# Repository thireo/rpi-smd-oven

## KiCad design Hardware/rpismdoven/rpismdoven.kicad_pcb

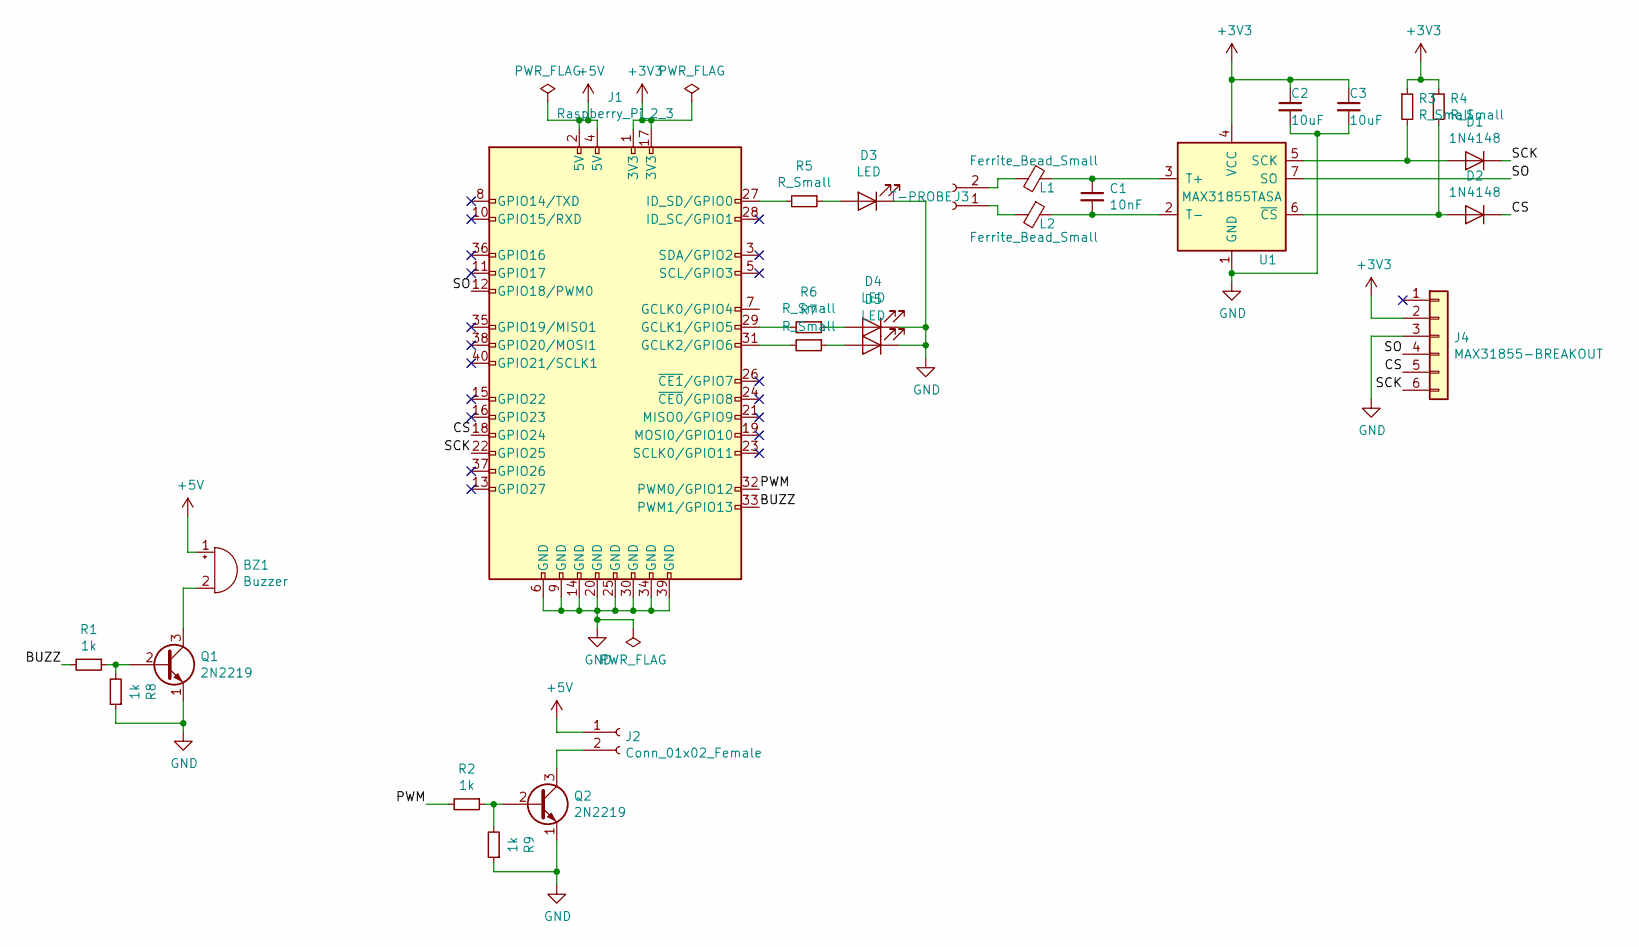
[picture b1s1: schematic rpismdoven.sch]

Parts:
BZ1: Buzzer; Buzzer_12x9.5RM7.6
C1: 10nF; C_0603_1608Metric
C2, C3: 10uF; C_0603_1608Metric
D1, D2: 1N4148; D_DO-35_SOD27_P7.62mm_Horizontal
D3, D4, D5: LED; D_1206_3216Metric
J1: Raspberry_Pi_2_3; PinSocket_2x20_P2.54mm_Vertical
J2: Conn_01x02_Female; TerminalBlock_bornier-2_P5.08mm
J3: T-PROBE; TerminalBlock_bornier-2_P5.08mm
J4: MAX31855-BREAKOUT; PinSocket_1x06_P2.54mm_Vertical
L1, L2: Ferrite_Bead_Small; L_0603_1608Metric
Q1, Q2: 2N2219; TO-92
R1, R2, R8, R9: 1k; R_0603_1608Metric
R3, R4, R5, R6, R7: R_Small; R_0603_1608Metric
U1: MAX31855TASA; SOIC-8_3.9x4.9mm_P1.27mm

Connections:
+3V3: C2.1, C3.1, J1.1 (3V3), J1.17 (3V3), J4.2, R3.1, R4.1, U1.4 (VCC)
+5V: BZ1.1 (-), J1.2 (5V), J1.4 (5V), J2.1
/BUZZ: J1.33 (PWM1/GPIO13), R1.2
/CS: D2.1 (K), J1.18 (GPIO24), J4.5
/PWM: J1.32 (PWM0/GPIO12), R2.2
/SCK: D1.1 (K), J1.22 (GPIO25), J4.6
/SO: J1.12 (GPIO18/PWM0), J4.4, U1.7 (SO)
GND: C2.2, C3.2, D3.1 (K), D4.1 (K), D5.1 (K), J1.6 (GND), J1.9 (GND), J1.14 (GND), J1.20 (GND), J1.25 (GND), J1.30 (GND), J1.34 (GND), J1.39 (GND), J4.3, Q1.1 (E), Q2.1 (E), R8.1, R9.1, U1.1 (GND)
unnamed: BZ1.2 (+), Q1.3 (C)
unnamed: C1.1, L1.1, U1.3 (T+)
unnamed: C1.2, L2.1, U1.2 (T-)
unnamed: D1.2 (A), R3.2, U1.5 (SCK)
unnamed: D2.2 (A), R4.2, U1.6 (~CS~)
unnamed: D3.2 (A), R5.1
unnamed: D4.2 (A), R6.1
unnamed: D5.2 (A), R7.1
unnamed: J1.27 (ID_SD/GPIO0), R5.2
unnamed: J1.29 (GCLK1/GPIO5), R6.2
unnamed: J1.31 (GCLK2/GPIO6), R7.2
unnamed: J2.2, Q2.3 (C)
unnamed: J3.1, L2.2
unnamed: J3.2, L1.2
unnamed: Q1.2 (B), R1.1, R8.2
unnamed: Q2.2 (B), R2.1, R9.2

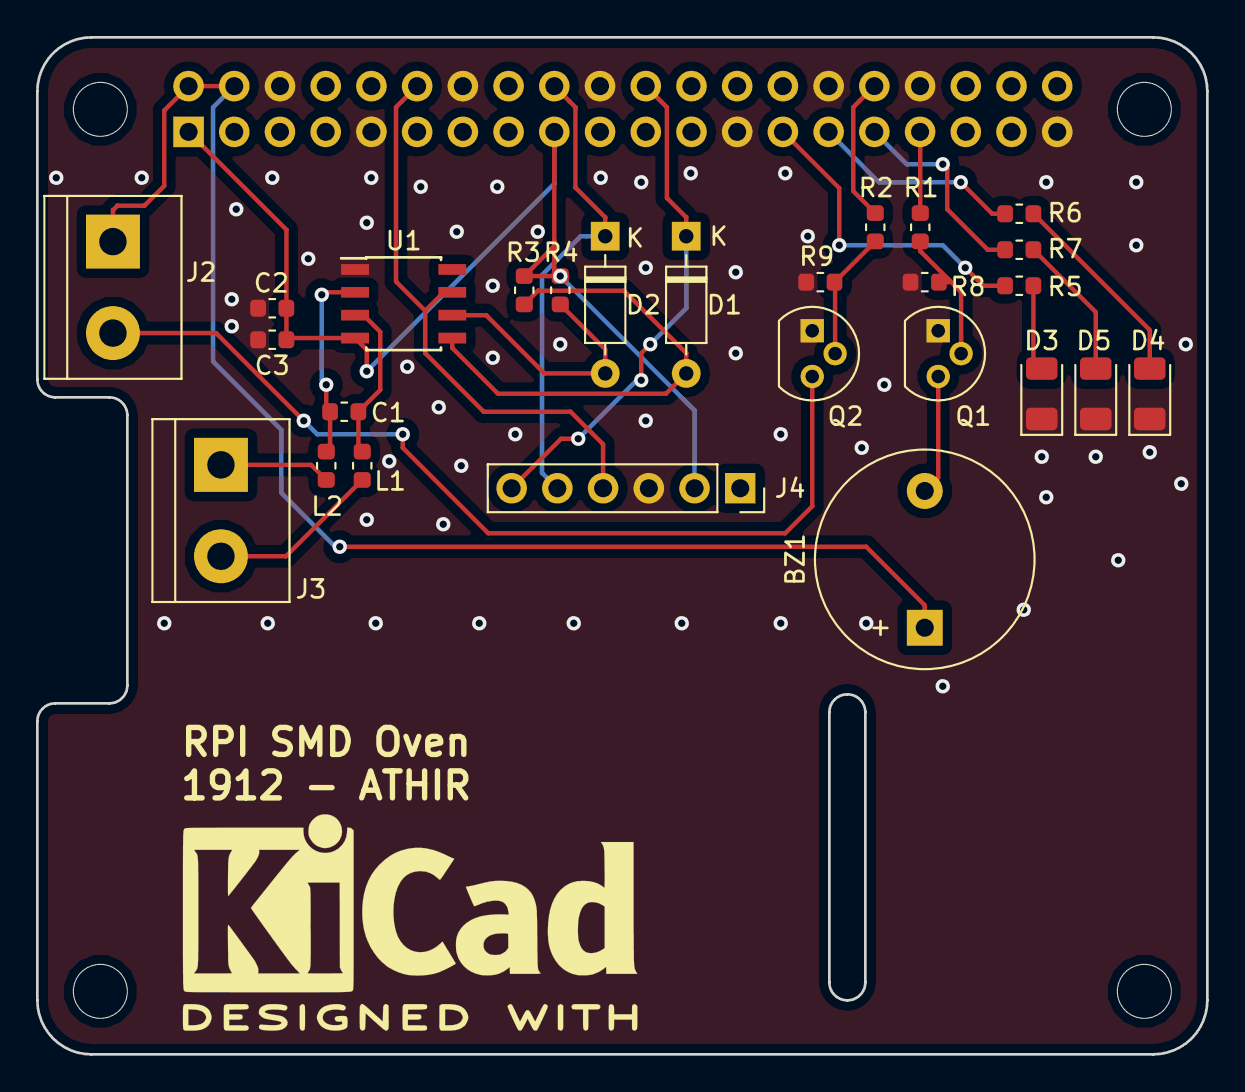
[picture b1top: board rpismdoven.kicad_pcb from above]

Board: 2 copper layers, 65.0 x 56.5 mm, 27 parts (1 on the bottom side), 24 nets.

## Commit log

2019-02-14 Initial Python plotter commit
    Added first log
    Added initial Python log plotter.
2019-02-17 Now parses -f as filename
2019-02-23 Bugfixes ovenplotter
2019-02-25 New Features in ovenplotter + new reflow profile
2019-02-28 Even more features in ovenplotter
2019-02-28 added datafile
2019-03-04 pid controller + impulseresponse
2019-03-07 added first pid datafile
2019-03-12 initial HW commit
2019-03-12 bump hw
2019-03-13 First finished draft HW
2019-03-22 HW rev1
2019-04-05 added ibom
2019-06-16 Set theme jekyll-theme-midnight
2019-06-18 Added readme.md
2019-06-18 Removed old README.md
2020-08-21 Sorry future me
2020-08-21 Sorry
